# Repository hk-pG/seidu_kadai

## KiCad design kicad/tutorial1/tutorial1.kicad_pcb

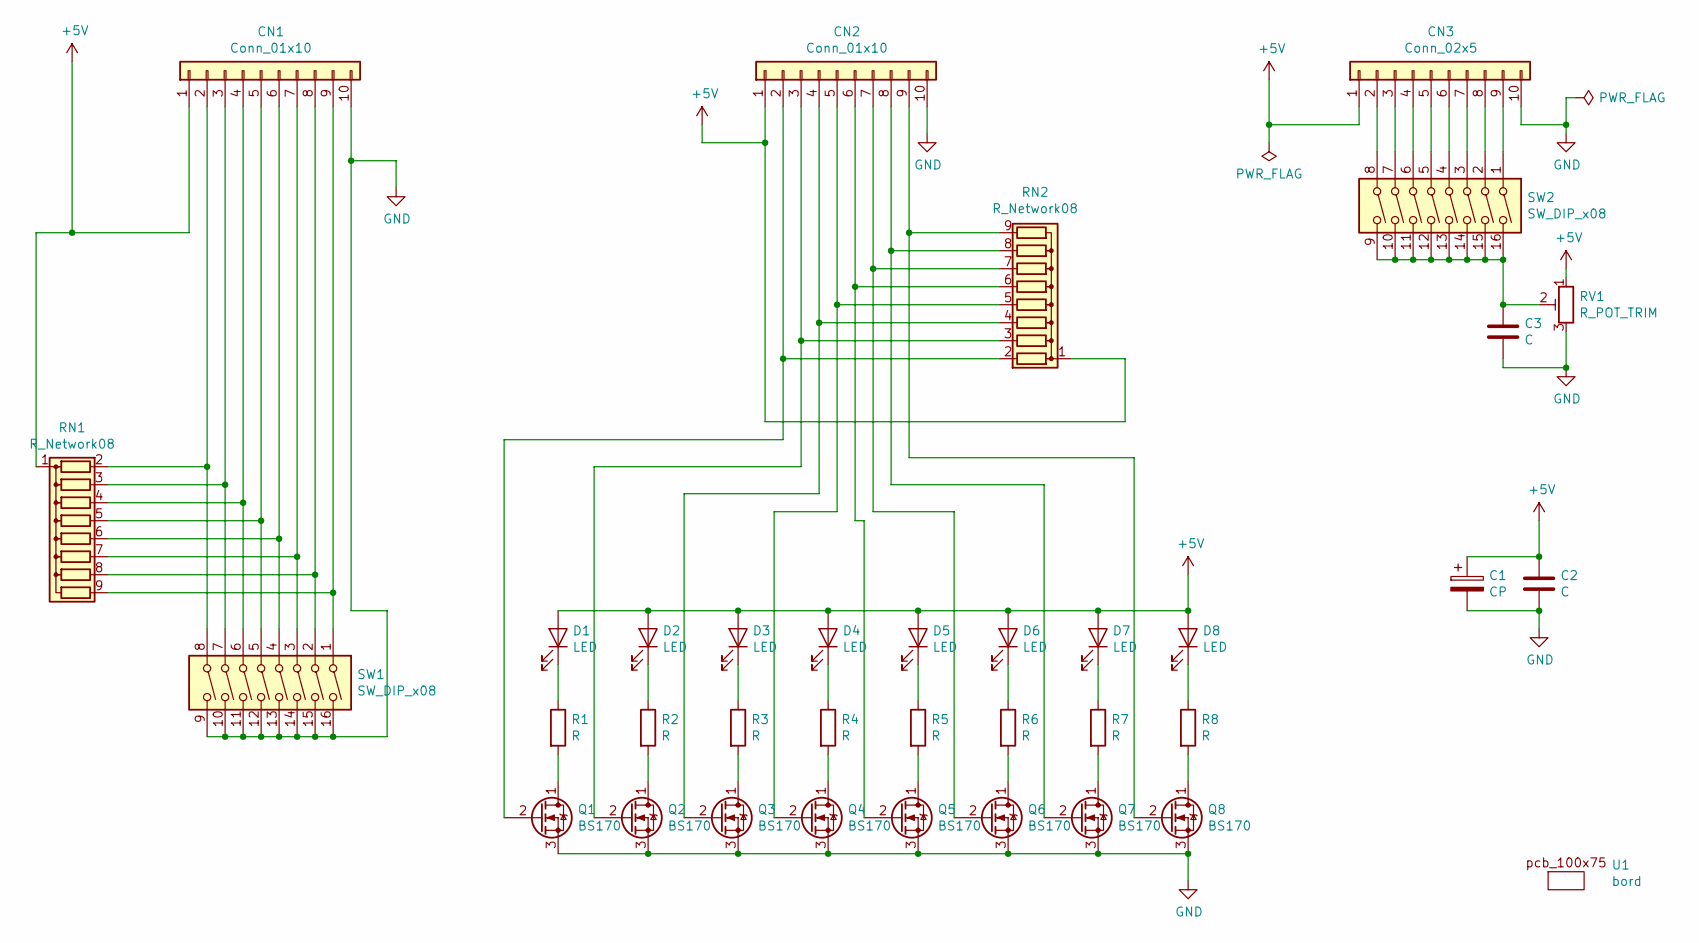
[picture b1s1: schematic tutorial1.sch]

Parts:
C1: CP; CP_Radial_D5.0mm_P2.00mm
C2, C3: C; C_Disc_D5.0mm_W2.5mm_P2.50mm
CN1, CN2: Conn_01x10; BH-10SG
CN3: Conn_02x5; BH-10SG
D1, D2, D3, D4, D5, D6, D7, D8: LED; LED_D3.0mm
Q1, Q2, Q3, Q4, Q5, Q6, Q7, Q8: BS170; TO-92_Inline
R1, R2, R3, R4, R5, R6, R7, R8: R; R_250mWmono-STD
RN1, RN2: R_Network08; R_Array_SIP9
RV1: R_POT_TRIM; Potentiometer_Vishay_148-149_Single_Horizontal
SW1, SW2: SW_DIP_x08; SW_DIP_x8_W7.62mm_Slide
U1: bord; pcb_100x75mm

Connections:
+5V: C1.1, C2.1, CN1.1, CN2.1, CN3.1, D1.2 (A), D2.2 (A), D3.2 (A), D4.2 (A), D5.2 (A), D6.2 (A), D7.2 (A), D8.2 (A), RN1.1 (common), RN2.1 (common), RV1.1
GND: C1.2, C2.2, C3.2, CN1.10, CN2.10, CN3.10, Q1.3 (S), Q2.3 (S), Q3.3 (S), Q4.3 (S), Q5.3 (S), Q6.3 (S), Q7.3 (S), Q8.3 (S), RV1.3, SW1.9, SW1.10, SW1.11, SW1.12, SW1.13, SW1.14, SW1.15, SW1.16
unnamed: C3.1, RV1.2, SW2.9, SW2.10, SW2.11, SW2.12, SW2.13, SW2.14, SW2.15, SW2.16
unnamed: CN1.2, RN1.2 (R1), SW1.8
unnamed: CN1.3, RN1.3 (R2), SW1.7
unnamed: CN1.4, RN1.4 (R3), SW1.6
unnamed: CN1.5, RN1.5 (R4), SW1.5
unnamed: CN1.6, RN1.6 (R5), SW1.4
unnamed: CN1.7, RN1.7 (R6), SW1.3
unnamed: CN1.8, RN1.8 (R7), SW1.2
unnamed: CN1.9, RN1.9 (R8), SW1.1
unnamed: CN2.2, Q1.2 (G), RN2.2 (R1)
unnamed: CN2.3, Q2.2 (G), RN2.3 (R2)
unnamed: CN2.4, Q3.2 (G), RN2.4 (R3)
unnamed: CN2.5, Q4.2 (G), RN2.5 (R4)
unnamed: CN2.6, Q5.2 (G), RN2.6 (R5)
unnamed: CN2.7, Q6.2 (G), RN2.7 (R6)
unnamed: CN2.8, Q7.2 (G), RN2.8 (R7)
unnamed: CN2.9, Q8.2 (G), RN2.9 (R8)
unnamed: CN3.2, SW2.8
unnamed: CN3.3, SW2.7
unnamed: CN3.4, SW2.6
unnamed: CN3.5, SW2.5
unnamed: CN3.6, SW2.4
unnamed: CN3.7, SW2.3
unnamed: CN3.8, SW2.2
unnamed: CN3.9, SW2.1
unnamed: D1.1 (K), R1.1
unnamed: D2.1 (K), R2.1
unnamed: D3.1 (K), R3.1
unnamed: D4.1 (K), R4.1
unnamed: D5.1 (K), R5.1
unnamed: D6.1 (K), R6.1
unnamed: D7.1 (K), R7.1
unnamed: D8.1 (K), R8.1
unnamed: Q1.1 (D), R1.2
unnamed: Q2.1 (D), R2.2
unnamed: Q3.1 (D), R3.2
unnamed: Q4.1 (D), R4.2
unnamed: Q5.1 (D), R5.2
unnamed: Q6.1 (D), R6.2
unnamed: Q7.1 (D), R7.2
unnamed: Q8.1 (D), R8.2

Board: 2 copper layers, 36 parts (0 on the bottom side), 43 nets, no tracks yet.

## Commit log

2022-10-08 add name and mark
2022-10-19 copied sample
2022-11-20 kicad
2022-11-24 save components
2022-11-25 before layerd
2022-11-27 sync
2022-12-04 autocad
2022-12-08 exception
2022-12-08 remove .dsstore
2022-12-08 make png data graph
2022-12-08 start kadai4
2022-12-08 kadai4
2022-12-09 haisen
2022-12-09 before net apply
2022-12-09 after net and ground
